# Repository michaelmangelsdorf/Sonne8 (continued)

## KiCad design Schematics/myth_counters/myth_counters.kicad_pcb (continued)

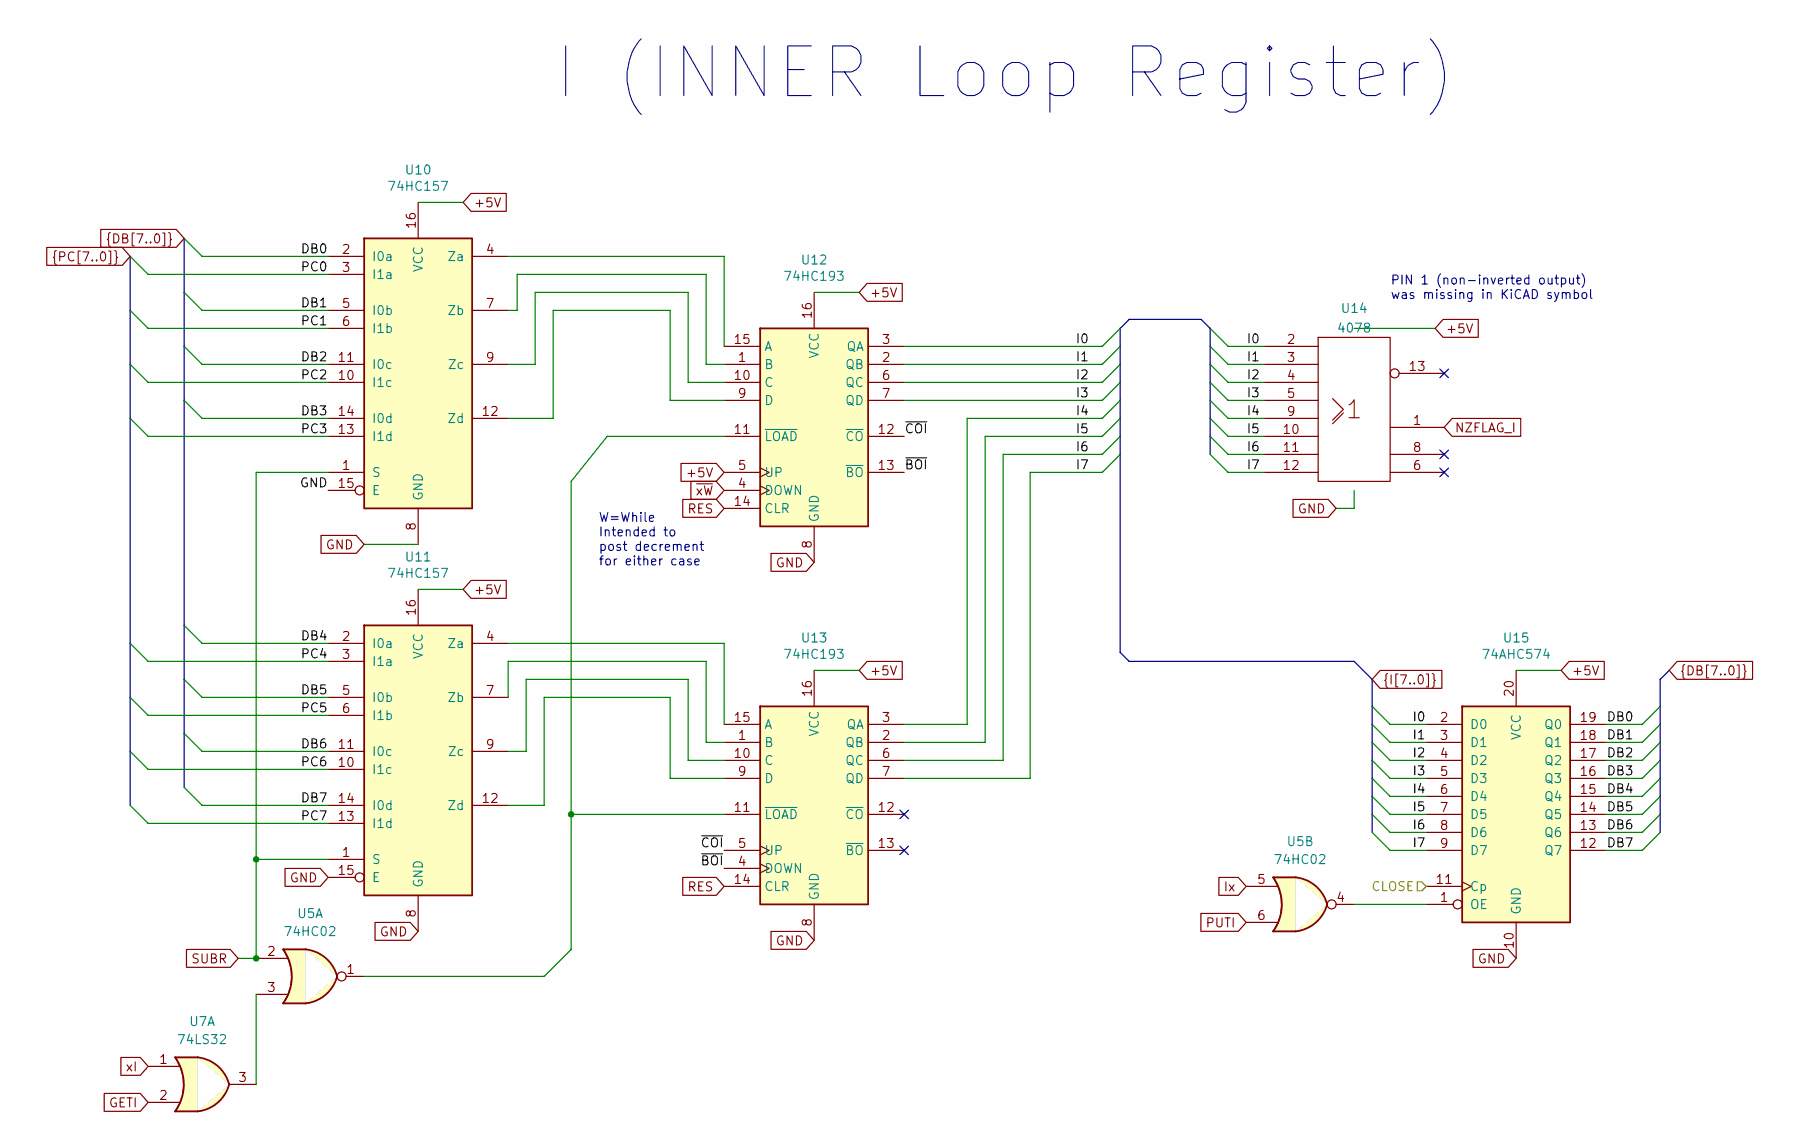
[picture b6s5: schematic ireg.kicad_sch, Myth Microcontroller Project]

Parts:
U5: 74HC02; DIP-14_W7.62mm_LongPads
U7: 74LS32; DIP-14_W7.62mm_LongPads
U10, U11: 74HC157; DIP-16_W7.62mm_Socket_LongPads
U12, U13: 74HC193; DIP-16_W7.62mm_Socket_LongPads
U14: 4078; DIP-14_W7.62mm_Socket_LongPads
U15: 74AHC574; DIP-20_W7.62mm_Socket_LongPads

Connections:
+5V: U10.16 (VCC), U11.16 (VCC), U12.5 (UP), U12.16 (VCC), U13.16 (VCC), U14.14 (Vdd), U15.20 (VCC); also elsewhere on the board
/I Register/CLOSE: U15.11 (Cp)
/I Register/~BOI: U12.13 (~BO), U13.4 (DOWN)
/I Register/~COI: U12.12 (~CO), U13.5 (UP)
DB0: U10.2 (I0a), U15.19 (Q0); also elsewhere on the board
DB1: U10.5 (I0b), U15.18 (Q1); also elsewhere on the board
DB2: U10.11 (I0c), U15.17 (Q2); also elsewhere on the board
DB3: U10.14 (I0d), U15.16 (Q3); also elsewhere on the board
DB4: U11.2 (I0a), U15.15 (Q4); also elsewhere on the board
DB5: U11.5 (I0b), U15.14 (Q5); also elsewhere on the board
DB6: U11.11 (I0c), U15.13 (Q6); also elsewhere on the board
DB7: U11.14 (I0d), U15.12 (Q7); also elsewhere on the board
GETI: U7.2
GND: U10.8 (GND), U10.15 (E), U11.8 (GND), U11.15 (E), U12.8 (GND), U13.8 (GND), U14.7 (Vss), U15.10 (GND); also elsewhere on the board
I0: U12.3 (QA), U14.2, U15.2 (D0); also elsewhere on the board
I1: U12.2 (QB), U14.3, U15.3 (D1); also elsewhere on the board
I2: U12.6 (QC), U14.4, U15.4 (D2); also elsewhere on the board
I3: U12.7 (QD), U14.5, U15.5 (D3); also elsewhere on the board
I4: U13.3 (QA), U14.9, U15.6 (D4); also elsewhere on the board
I5: U13.2 (QB), U14.10, U15.7 (D5); also elsewhere on the board
I6: U13.6 (QC), U14.11, U15.8 (D6); also elsewhere on the board
I7: U13.7 (QD), U14.12, U15.9 (D7); also elsewhere on the board
Ix: U5.5
NZFLAG_I: U14.1; also elsewhere on the board
unnamed: U5.3, U7.3
unnamed: U10.4 (Za), U12.15 (A)
unnamed: U10.7 (Zb), U12.1 (B)
unnamed: U10.9 (Zc), U12.10 (C)
unnamed: U10.12 (Zd), U12.9 (D)
unnamed: U11.4 (Za), U13.15 (A)
unnamed: U11.7 (Zb), U13.1 (B)
unnamed: U11.9 (Zc), U13.10 (C)
unnamed: U11.12 (Zd), U13.9 (D)
unnamed: U5.1, U12.11 (~LOAD), U13.11 (~LOAD)
unnamed: U5.4, U15.1 (OE)
PC0: U10.3 (I1a); also elsewhere on the board
PC1: U10.6 (I1b); also elsewhere on the board
PC2: U10.10 (I1c); also elsewhere on the board
PC3: U10.13 (I1d); also elsewhere on the board
PC4: U11.3 (I1a); also elsewhere on the board
PC5: U11.6 (I1b); also elsewhere on the board
PC6: U11.10 (I1c); also elsewhere on the board
PC7: U11.13 (I1d); also elsewhere on the board
PUTI: U5.6
RES: U12.14 (CLR), U13.14 (CLR); also elsewhere on the board
SUBR: U5.2, U10.1 (S), U11.1 (S)
xI: U7.1
~xW: U12.4 (DOWN)

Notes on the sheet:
PIN 1 (non-inverted output) was missing in KiCAD symbol
W=While Intended to post decrement for either case
I (INNER Loop Register)

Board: 2 copper layers, 48 parts (0 on the bottom side), 90 nets, no tracks yet.

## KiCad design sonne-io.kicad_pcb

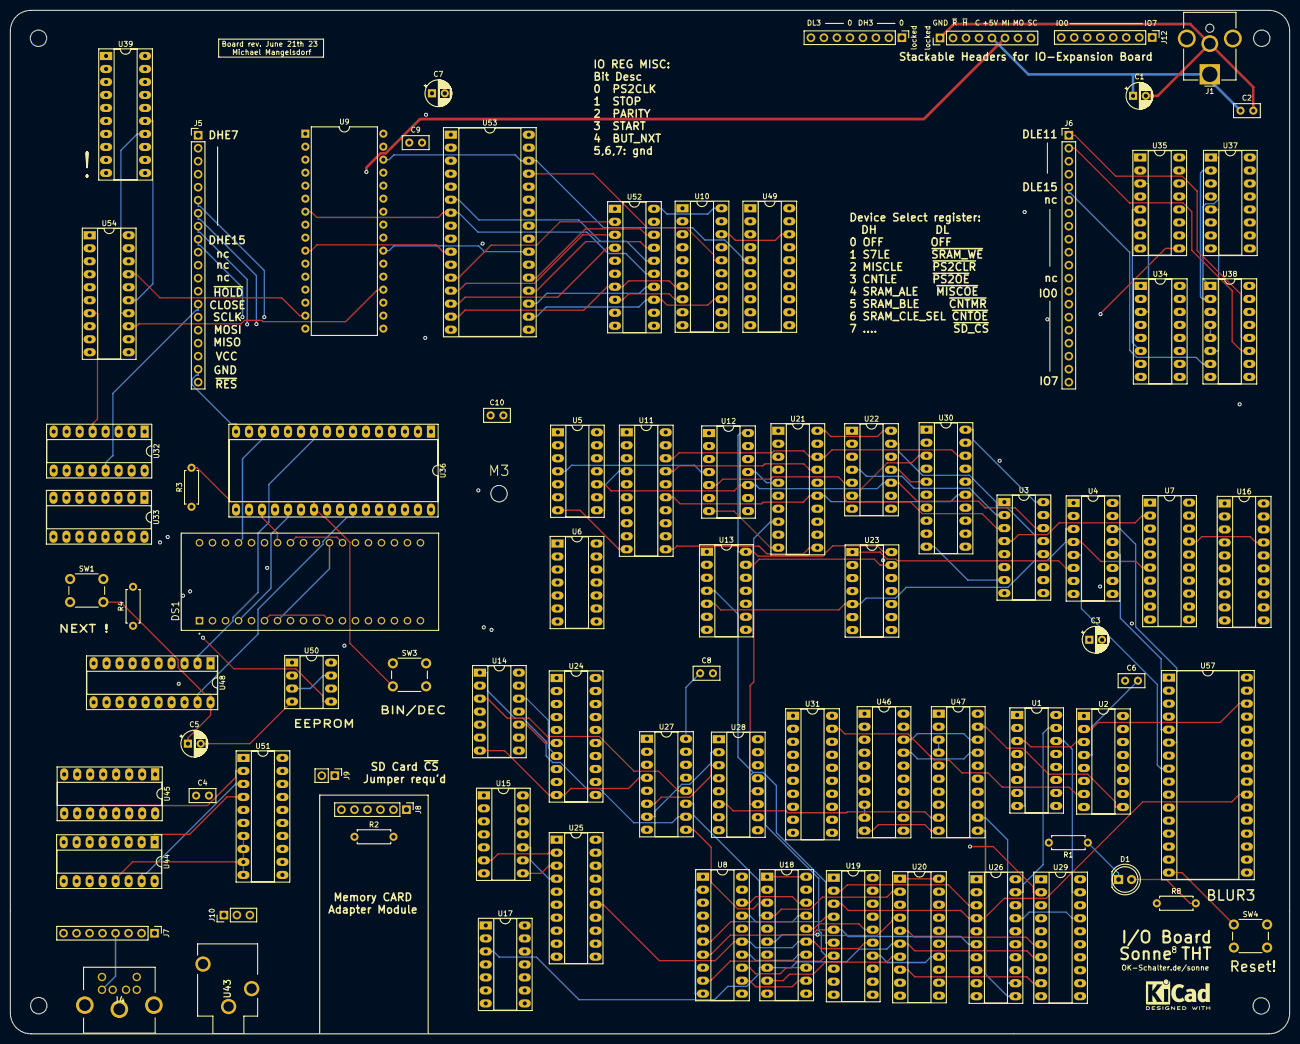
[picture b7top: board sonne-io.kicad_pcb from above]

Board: 4 copper layers, 250.0 x 200.0 mm, 83 parts (0 on the bottom side), 226 nets.

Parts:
C1, C3, C5, C7: C_Polarized_Small; CP_Radial_D5.0mm_P2.50mm
C2, C4, C6, C8, C9, C10: C_Small; C_Disc_D5.0mm_W2.5mm_P2.50mm
D1: LED; LED_D5.0mm
DS1: CA56-11EWA; LED_CA56-11EWA
J1: Barrel_Jack; BarrelJack_CUI_PJ-063AH_Horizontal_CircularHoles
J4: KMDGX-6S-BS; KMDGX6SBS
J5, J6: Conn_01x20_Male; PinHeader_1x20_P2.54mm_Vertical
J7, J12: Conn_01x08_Male; PinHeader_1x08_P2.54mm_Vertical
J8: Conn_01x06_Female; PinHeader_1x06_P2.54mm_Vertical
J9: Conn_01x02_Male; PinHeader_1x02_P2.54mm_Vertical
J10: Conn_01x03_Male; PinHeader_1x03_P2.54mm_Vertical
R1: 220; R_Axial_DIN0207_L6.3mm_D2.5mm_P7.62mm_Horizontal
R2: 100 Ohm; R_Axial_DIN0207_L6.3mm_D2.5mm_P7.62mm_Horizontal
R3: R_Small; R_Axial_DIN0207_L6.3mm_D2.5mm_P7.62mm_Horizontal
R4, R8: 1k; R_Axial_DIN0207_L6.3mm_D2.5mm_P7.62mm_Horizontal
SW1, SW4: SW_RES; SW_PUSH_6mm_H4.3mm
SW3: SW_BINDEC; SW_PUSH_6mm_H4.3mm
U1, U2, U37, U38: 74LS138; DIP-16_W7.62mm_Socket_LongPads
U3, U4: 74LS283; DIP-16_W7.62mm_Socket_LongPads
U5, U6: 74LS08; DIP-14_W7.62mm_Socket_LongPads
U7, U8, U11, U16, U18, U19, U20, U21, U24, U25, U26, U29, U30, U31, U46, U47: 74HC245; DIP-20_W7.62mm_Socket_LongPads
U9: AS6C4008-55PCN; DIP-32_W15.24mm
U10, U48, U49, U52: 74HC273; DIP-20_W7.62mm_Socket_LongPads
U12, U13: 74LS86; DIP-14_W7.62mm_Socket_LongPads
U14, U15, U17: 74AHC04; DIP-14_W7.62mm_Socket_LongPads
U22, U23: 74LS32; DIP-14_W7.62mm_Socket_LongPads
U27, U28: 74LS85; DIP-16_W7.62mm_Socket_LongPads
U32: 74HC590; DIP-16_W7.62mm_Socket_LongPads
U33, U34, U35: 74HC238; DIP-16_W7.62mm_Socket_LongPads
U36, U53: SST39SF040; DIP-32_W15.24mm_Socket_LongPads
U39: 74LS573; DIP-20_W7.62mm_Socket_LongPads
U43: SJ1-3513N; SJ13513N
U44, U45: 74HC595; DIP-16_W7.62mm_Socket_LongPads
U50: 25LCxxx; DIP-8_W7.62mm_Socket_LongPads
U51, U54: 74LS574; DIP-20_W7.62mm_Socket_LongPads
U57: 27C080; DIP-32_W15.24mm_Socket_LongPads
locked: Conn_01x08_Male; PinHeader_1x08_P2.54mm_Vertical
locked#2: Conn_01x08_Male; PinHeader_1x08_P2.54mm_Vertical

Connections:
/AD0: U9.12 (A0), U52.2 (Q0), U53.12 (A0)
/AD1: U9.11 (A1), U52.5 (Q1), U53.11 (A1)
/AD2: U9.10 (A2), U52.6 (Q2), U53.10 (A2)
/AD3: U9.9 (A3), U52.9 (Q3), U53.9 (A3)
/AD4: U9.8 (A4), U52.12 (Q4), U53.8 (A4)
/AD5: U9.7 (A5), U52.15 (Q5), U53.7 (A5)
/AD6: U9.6 (A6), U52.16 (Q6), U53.6 (A6)
/AD7: U9.5 (A7), U52.19 (Q7), U53.5 (A7)
/AD8: U9.27 (A8), U10.2 (Q0), U53.27 (A8)
/AD9: U9.26 (A9), U10.5 (Q1), U53.26 (A9)
/AD10: U9.23 (A10), U10.6 (Q2), U53.23 (A10)
/AD11: U9.25 (A11), U10.9 (Q3), U53.25 (A11)
/AD12: U9.4 (A12), U10.12 (Q4), U53.4 (A12)
/AD13: U9.28 (A13), U10.15 (Q5), U53.28 (A13)
/AD14: U9.3 (A14), U10.16 (Q6), U53.29 (A14)
/AD15: U9.31 (A15), U10.19 (Q7), U53.3 (A15)
/AD16: U9.2 (A16), U49.2 (Q0), U53.2 (A16)
/AD17: U9.30 (A17), U49.5 (Q1), U53.30 (A17)
/AD18: U9.1 (A18), U49.6 (Q2), U53.1 (A18)
/ADD: U2.12 (O3), U7.19 (CE)
/AEB: U2.9 (O6), U47.19 (CE)
/AGB: U2.7 (O7), U31.19 (CE)
/ALB: U2.10 (O5), U46.19 (CE)
/AND: U2.15 (O0), U11.19 (CE)
/AND0: U5.3, U11.2 (A0)
/AND1: U5.6, U11.3 (A1)
/AND2: U5.8, U11.4 (A2)
/AND3: U5.11, U11.5 (A3)
/AND4: U6.3, U11.6 (A4)
/AND5: U6.6, U11.7 (A5)
/AND6: U6.8, U11.8 (A6)
/AND7: U6.11, U11.9 (A7)
/BIN_OPC0: U1.1 (A0), U2.1 (A0), U57.2 (A16)
/BIN_OPC1: U1.2 (A1), U2.2 (A1), U57.30 (A17)
/BIN_OPC2: U1.3 (A2), U2.3 (A2), U57.31 (A18)
/BIN_OPC3: U1.4 (E1), U2.6 (E3), U57.1 (A19)
/BUT_NXT: R4.2, SW1.1, U51.6 (D4)
/CLOSE: J5.14, U32.11 (CPC), U32.13 (CPR), locked.4
/CNTLE: U35.12 (Y3), U54.11 (Cp)
/CYB: U2.11 (O4), U16.19 (CE)
/DH0: U34.1 (A0), U35.1 (A0), locked#2.1
/DH1: U34.2 (A1), U35.2 (A1), locked#2.2
/DH2: U34.3 (A2), U35.3 (A2), locked#2.3
/DH3: U34.6 (G1), U35.4 (~G2A), U35.5 (~G2B), locked#2.4
/DHE7: J5.1, U35.7 (Y7)
/DHE8: J5.2, U34.15 (Y0)
/DHE9: J5.3, U34.14 (Y1)
/DHE10: J5.4, U34.13 (Y2)
/DHE11: J5.5, U34.12 (Y3)
/DHE12: J5.6, U34.11 (Y4)
/DHE13: J5.7, U34.10 (Y5)
/DHE14: J5.8, U34.9 (Y6)
/DHE15: J5.9, U34.7 (Y7)
/DL0: U37.1 (A0), U38.1 (A0), locked#2.5
/DL1: U37.2 (A1), U38.2 (A1), locked#2.6
/DL2: U37.3 (A2), U38.3 (A2), locked#2.7
/DL3: U37.4 (E1), U37.5 (E2), U38.6 (E3), locked#2.8
/DLE11: J6.1, U38.12 (O3)
/DLE12: J6.2, U38.11 (O4)
/DLE13: J6.3, U38.10 (O5)
/DLE14: J6.4, U38.9 (O6)
/DLE15: J6.5, U38.7 (O7)
/E0: DS1.32, U33.15 (Y0)
/E1: DS1.31, U33.14 (Y1)
/E2: DS1.23, U33.13 (Y2)
/E3: DS1.22, U33.12 (Y3)
/EOR: U2.13 (O2), U21.19 (CE)
/EOR0: U12.3, U21.2 (A0)
/EOR1: U12.6, U21.3 (A1)
/EOR2: U12.8, U21.4 (A2)
/EOR3: U12.11, U21.5 (A3)
/EOR4: U13.3, U21.6 (A4)
/EOR5: U13.6, U21.7 (A5)
/EOR6: U13.8, U21.8 (A6)
/EOR7: U13.11, U21.9 (A7)
/IDA: U1.15 (O0), U26.19 (CE)
/IDB: U1.14 (O1), U29.19 (CE)
/IO0: J6.13, J12.8, U9.13 (DQ0), U10.3 (D0), U39.19 (Q0), U48.3 (D0), U49.3 (D0), U51.19 (Q0), U52.3 (D0), U53.13 (D0), U54.19 (Q0)
/IO1: J6.14, J12.7, U9.14 (DQ1), U10.4 (D1), U39.18 (Q1), U48.4 (D1), U49.4 (D1), U51.18 (Q1), U52.4 (D1), U53.14 (D1), U54.18 (Q1)
/IO2: J6.15, J12.6, U9.15 (DQ2), U10.7 (D2), U39.17 (Q2), U48.7 (D2), U49.7 (D2), U51.17 (Q2), U52.7 (D2), U53.15 (D2), U54.17 (Q2)
/IO3: J6.16, J12.5, U9.17 (DQ3), U10.8 (D3), U39.16 (Q3), U48.8 (D3), U49.8 (D3), U51.16 (Q3), U52.8 (D3), U53.17 (D3), U54.16 (Q3)
/IO4: J6.17, J12.4, U9.18 (DQ4), U10.13 (D4), U39.15 (Q4), U48.13 (D4), U49.13 (D4), U51.15 (Q4), U52.13 (D4), U53.18 (D4), U54.15 (Q4)
/IO5: J6.18, J12.3, U9.19 (DQ5), U10.14 (D5), U39.14 (Q5), U48.14 (D5), U49.14 (D5), U51.14 (Q5), U52.14 (D5), U53.19 (D5), U54.14 (Q5)
/IO6: J6.19, J12.2, U9.20 (DQ6), U10.17 (D6), U39.13 (Q6), U48.17 (D6), U49.17 (D6), U51.13 (Q6), U52.17 (D6), U53.20 (D6), U54.13 (Q6)
/IO7: J6.20, J12.1, U9.21 (DQ7), U10.18 (D7), U39.12 (Q7), U48.18 (D7), U49.18 (D7), U51.12 (Q7), U52.18 (D7), U53.21 (D7), U54.12 (Q7)
/IOR: U2.14 (O1), U30.19 (CE)
/IOR0: U22.3, U30.2 (A0)
/IOR1: U22.6, U30.3 (A1)
/IOR2: U22.8, U30.4 (A2)
/IOR3: U22.11, U30.5 (A3)
/IOR4: U23.3, U30.6 (A4)
/IOR5: U23.6, U30.7 (A5)
/IOR6: U23.8, U30.8 (A6)
/IOR7: U23.11, U30.9 (A7)
/MISCLE: U35.13 (Y2), U51.11 (Cp)
/MISO: J5.17, J8.3, U50.2 (MISO), locked.6
/MOSI: J5.16, J8.4, U50.5 (MOSI), locked.7
/NOTRA0: U14.2, U24.2 (A0)
/NOTRA1: U14.4, U24.3 (A1)
/NOTRA2: U14.6, U24.4 (A2)
/NOTRA3: U14.8, U24.5 (A3)
/NOTRA4: U14.10, U24.6 (A4)
/NOTRA5: U14.12, U24.7 (A5)
/NOTRA6: U15.2, U24.8 (A6)
/NOTRA7: U15.4, U24.9 (A7)
/NOTRB0: U15.6, U25.2 (A0)
/NOTRB1: U15.8, U25.3 (A1)
/NOTRB2: U15.10, U25.4 (A2)
/NOTRB3: U15.12, U25.5 (A3)
/NOTRB4: U17.2, U25.6 (A4)
/NOTRB5: U17.4, U25.7 (A5)
/NOTRB6: U17.6, U25.8 (A6)
/NOTRB7: U17.8, U25.9 (A7)
/OCA: U1.13 (O2), U24.19 (CE)
/OCB: U1.12 (O3), U25.19 (CE)
/PARITY: U44.1 (QB), U51.4 (D2)
/PS2CLK: J4.6, J7.5, U44.11 (SRCLK), U44.12 (RCLK), U45.11 (SRCLK), U45.12 (RCLK), U51.2 (D0)
/PS2DATA: J4.1, J7.1, U44.14 (SER)
/PSB0: U39.2 (D0), U45.1 (QB)
/PSB1: U39.3 (D1), U45.15 (QA)
/PSB2: U39.4 (D2), U44.7 (QH)
/PSB3: U39.5 (D3), U44.6 (QG)
/PSB4: U39.6 (D4), U44.5 (QF)
/PSB5: U39.7 (D5), U44.4 (QE)
/PSB6: U39.8 (D6), U44.3 (QD)
/PSB7: U39.9 (D7), U44.2 (QC)
/Q0: U32.15 (Q0), U54.2 (D0)
/Q1: U32.1 (Q1), U54.3 (D1)
/Q2: U32.2 (Q2), U54.4 (D2)
/Q3: U32.3 (Q3), U54.5 (D3)
/Q4: U32.4 (Q4), U54.6 (D4)
/Q5: U32.5 (Q5), U54.7 (D5)
/Q6: U32.6 (Q6), U33.1 (A0), U36.12 (A0), U54.8 (D6)
/Q7: U32.7 (Q7), U33.2 (A1), U36.11 (A1), U54.9 (D7)
/R0: U7.18 (B0), U8.18 (B0), U11.18 (B0), U16.18 (B0), U18.18 (B0), U19.18 (B0), U20.18 (B0), U21.18 (B0), U24.18 (B0), U25.18 (B0), U26.18 (B0), U29.18 (B0), U30.18 (B0), U31.18 (B0), U46.18 (B0), U47.18 (B0), U57.13 (D0)
/R1: U7.17 (B1), U8.17 (B1), U11.17 (B1), U16.17 (B1), U18.17 (B1), U19.17 (B1), U20.17 (B1), U21.17 (B1), U24.17 (B1), U25.17 (B1), U26.17 (B1), U29.17 (B1), U30.17 (B1), U31.17 (B1), U46.17 (B1), U47.17 (B1), U57.14 (D1)
/R2: U7.16 (B2), U8.16 (B2), U11.16 (B2), U16.16 (B2), U18.16 (B2), U19.16 (B2), U20.16 (B2), U21.16 (B2), U24.16 (B2), U25.16 (B2), U26.16 (B2), U29.16 (B2), U30.16 (B2), U31.16 (B2), U46.16 (B2), U47.16 (B2), U57.15 (D2)
/R3: U7.15 (B3), U8.15 (B3), U11.15 (B3), U16.15 (B3), U18.15 (B3), U19.15 (B3), U20.15 (B3), U21.15 (B3), U24.15 (B3), U25.15 (B3), U26.15 (B3), U29.15 (B3), U30.15 (B3), U31.15 (B3), U46.15 (B3), U47.15 (B3), U57.17 (D3)
/R4: U7.14 (B4), U8.14 (B4), U11.14 (B4), U16.14 (B4), U18.14 (B4), U19.14 (B4), U20.14 (B4), U21.14 (B4), U24.14 (B4), U25.14 (B4), U26.14 (B4), U29.14 (B4), U30.14 (B4), U31.14 (B4), U46.14 (B4), U47.14 (B4), U57.18 (D4)
/R5: U7.13 (B5), U8.13 (B5), U11.13 (B5), U16.13 (B5), U18.13 (B5), U19.13 (B5), U20.13 (B5), U21.13 (B5), U24.13 (B5), U25.13 (B5), U26.13 (B5), U29.13 (B5), U30.13 (B5), U31.13 (B5), U46.13 (B5), U47.13 (B5), U57.19 (D5)
/R6: U7.12 (B6), U8.12 (B6), U11.12 (B6), U16.12 (B6), U18.12 (B6), U19.12 (B6), U20.12 (B6), U21.12 (B6), U24.12 (B6), U25.12 (B6), U26.12 (B6), U29.12 (B6), U30.12 (B6), U31.12 (B6), U46.12 (B6), U47.12 (B6), U57.20 (D6)
/R7: U7.11 (B7), U8.11 (B7), U11.11 (B7), U16.11 (B7), U18.11 (B7), U19.11 (B7), U20.11 (B7), U21.11 (B7), U24.11 (B7), U25.11 (B7), U26.11 (B7), U29.11 (B7), U30.11 (B7), U31.11 (B7), U46.11 (B7), U47.11 (B7), U57.21 (D7)
/RA0: U3.6 (B1), U5.1, U8.3 (A1), U12.1, U14.1, U22.1, U26.2 (A0), U27.10 (A0), U57.27 (A8)
/RA1: U3.2 (B2), U5.4, U8.4 (A2), U12.4, U14.3, U19.2 (A0), U22.4, U26.3 (A1), U27.12 (A1), U57.26 (A9)
/RA2: U3.15 (B3), U5.9, U8.5 (A3), U12.9, U14.5, U19.3 (A1), U22.9, U26.4 (A2), U27.13 (A2), U57.23 (A10)
/RA3: U3.11 (B4), U5.12, U8.6 (A4), U12.12, U14.9, U19.4 (A2), U22.12, U26.5 (A3), U27.15 (A3), U57.25 (A11)
/RA4: U4.6 (B1), U6.1, U8.7 (A5), U13.1, U14.11, U19.5 (A3), U23.1, U26.6 (A4), U28.10 (A0), U57.4 (A12)
/RA5: U4.2 (B2), U6.4, U8.8 (A6), U13.4, U14.13, U19.6 (A4), U23.4, U26.7 (A5), U28.12 (A1), U57.28 (A13)
/RA6: U4.15 (B3), U6.9, U8.9 (A7), U13.9, U15.1, U19.7 (A5), U23.9, U26.8 (A6), U28.13 (A2), U57.29 (A14)
/RA7: U4.11 (B4), U6.12, U13.12, U15.3, U19.8 (A6), U23.12, U26.9 (A7), U28.15 (A3), U57.3 (A15)
/RB0: U3.5 (A1), U5.2, U12.2, U15.5, U18.3 (A1), U22.2, U27.9 (B0), U29.2 (A0), U57.12 (A0)
/RB1: U3.3 (A2), U5.5, U12.5, U15.9, U18.4 (A2), U20.2 (A0), U22.5, U27.11 (B1), U29.3 (A1), U57.11 (A1)
/RB2: U3.14 (A3), U5.10, U12.10, U15.11, U18.5 (A3), U20.3 (A1), U22.10, U27.14 (B2), U29.4 (A2), U57.10 (A2)
/RB3: U3.12 (A4), U5.13, U12.13, U15.13, U18.6 (A4), U20.4 (A2), U22.13, U27.1 (B3), U29.5 (A3), U57.9 (A3)
/RB4: U4.5 (A1), U6.2, U13.2, U17.1, U18.7 (A5), U20.5 (A3), U23.2, U28.9 (B0), U29.6 (A4), U57.8 (A4)
/RB5: U4.3 (A2), U6.5, U13.5, U17.3, U18.8 (A6), U20.6 (A4), U23.5, U28.11 (B1), U29.7 (A5), U57.7 (A5)
/RB6: U4.14 (A3), U6.10, U13.10, U17.5, U18.9 (A7), U20.7 (A5), U23.10, U28.14 (B2), U29.8 (A6), U57.6 (A6)
/RB7: U4.12 (A4), U6.13, U13.13, U17.9, U20.8 (A6), U23.13, U28.1 (B3), U29.9 (A7), U57.5 (A7)
/RING: J10.1, U43.3 (RING)
/S7D0: U36.10 (A2), U48.2 (Q0)
/S7D1: U36.9 (A3), U48.5 (Q1)
/S7D2: U36.8 (A4), U48.6 (Q2)
/S7D3: U36.7 (A5), U48.9 (Q3)
/S7D4: U36.6 (A6), U48.12 (Q4)
/S7D5: U36.5 (A7), U48.15 (Q5)
/S7D6: U36.27 (A8), U48.16 (Q6)
/S7D7: U36.26 (A9), U48.19 (Q7)
/S7LE: U35.14 (Y1), U48.11 (Cp)
/SCLK: J5.15, J8.5, R2.1, U50.6 (SCK), locked.8
/SLA: U1.11 (O4), U8.19 (CE)
/SLB: U1.10 (O5), U18.19 (CE)
/SLEEVE: J10.2, U43.1 (SLEEVE)
/SRA: U1.9 (O6), U19.19 (CE)
/SRAM_ALE: U35.11 (Y4), U52.11 (Cp)
/SRAM_BLE: U10.11 (Cp), U35.10 (Y5)
/SRAM_CLE_SEL: U35.9 (Y6), U49.11 (Cp)
/SRB: U1.7 (O7), U20.19 (CE)
/START: U45.2 (QC), U51.5 (D3)
/STOP: U44.15 (QA), U51.3 (D1)
/Sa: DS1.20, DS1.25, DS1.29, DS1.34, U36.13 (D0)
/Sb: DS1.19, DS1.24, DS1.28, DS1.33, U36.14 (D1)
/Sc: DS1.3, DS1.8, DS1.12, DS1.17, U36.15 (D2)
/Sd: DS1.2, DS1.6, DS1.11, DS1.15, U36.17 (D3)
/Sdp: DS1.4, DS1.9, DS1.13, DS1.18, U36.21 (D7)
/Se: DS1.1, DS1.5, DS1.10, DS1.14, U36.18 (D4)
/Sf: DS1.21, DS1.27, DS1.30, DS1.36, U36.19 (D5)
/Sg: DS1.7, DS1.16, DS1.26, DS1.35, U36.20 (D6)
/TIP: J10.3, U43.2 (TIP)
/~CNTMR: U32.10 (~MRC), U37.10 (O5)
/~CNTOE: U37.9 (O6), U54.1 (OE)
/~EEP_CS: U38.15 (O0), U50.1 (~CS)
/~HOLD: J5.13, locked.3
/~MISCOE: U37.11 (O4), U51.1 (OE)
/~PS2CLR: U37.13 (O2), U44.10 (~SRCLR), U45.10 (~SRCLR)
/~PS2OE: U37.12 (O3), U39.1 (OE)
/~RES: J5.20, R8.1, SW4.2, U48.1 (~Mr), locked.2
/~SD_CS: J9.2, U37.7 (O7)
/~SRAMA_CLR: U10.1 (~Mr), U38.14 (O1), U49.1 (~Mr), U52.1 (~Mr)
/~SRAM_OE: U9.24 (OE#), U38.13 (O2), U53.24 (OE)
/~SRAM_WE: U9.29 (WE#), U37.14 (O1)
GND: C1.2, C2.2, C3.2, C4.2, C5.2, C6.2, C7.2, C8.2, C9.2, C10.2, J1.2, J4.3, J4.MH1, J4.MH2, J4.MH3, J5.19, J7.3, J7.7, J7.8, J8.1, R1.2, R2.2, R4.1, SW3.1, SW4.1, U1.5 (E2), U1.8 (GND), U2.4 (E1), U2.5 (E2), U2.8 (GND), U3.7 (C0), U3.8 (GND), U4.8 (GND), U5.7 (GND), U6.7 (GND), U7.10 (GND), U8.2 (A0), U8.10 (GND), U9.16 (VSS), U10.10 (GND), U11.10 (GND), U12.7 (GND), U13.7 (GND), U14.7 (GND), U15.7 (GND), U16.3 (A1), U16.4 (A2), U16.5 (A3), U16.6 (A4), U16.7 (A5), U16.8 (A6), U16.9 (A7), U16.10 (GND), U17.7 (GND), U17.13, U18.2 (A0), U18.10 (GND), U19.9 (A7), U19.10 (GND), U20.9 (A7), U20.10 (GND), U21.10 (GND), U22.7 (GND), U23.7 (GND), U24.10 (GND), U25.10 (GND), U26.10 (GND), U27.2 (Ia<b), U27.3 (Ia=b), U27.4 (Ia>b), U27.8 (GND), U28.8 (GND), U29.10 (GND), U30.10 (GND), U31.10 (GND), U32.8 (GND), U32.12 (~CE), U32.14 (~OE), U33.3 (A2), U33.4 (~G2A), U33.5 (~G2B), U33.8 (GND), U34.4 (~G2A), U34.5 (~G2B), U34.8 (GND), U35.8 (GND), U36.1 (A18), U36.2 (A16), U36.3 (A15), U36.4 (A12), U36.16 (GND), U36.22 (CE), U36.24 (OE), U36.25 (A11), U36.28 (A13), U36.29 (A14), U36.30 (A17), U37.8 (GND), U38.4 (E1), U38.5 (E2), U38.8 (GND), U39.10 (GND), U44.8 (GND), U44.13 (~OE), U45.8 (GND), U45.13 (~OE), U46.10 (GND), U47.10 (GND), U48.10 (GND), U49.10 (GND), U50.4 (GND), U51.7 (D5), U51.8 (D6), U51.9 (D7), U51.10 (GND), U52.10 (GND), U53.16 (GND), U54.10 (GND), U57.16 (GND), U57.22 (~CE), U57.24 (~OE), locked.1
unnamed: D1.1 (K), R1.1
unnamed: J4.2, J7.2
unnamed: J4.8, J7.6
unnamed: J8.6, J9.1
unnamed: U3.9 (C4), U4.7 (C0)
unnamed: U3.4 (S1), U7.2 (A0)
unnamed: U3.1 (S2), U7.3 (A1)
unnamed: U3.13 (S3), U7.4 (A2)
unnamed: U3.10 (S4), U7.5 (A3)
unnamed: U4.4 (S1), U7.6 (A4)
unnamed: U4.1 (S2), U7.7 (A5)
unnamed: U4.13 (S3), U7.8 (A6)
unnamed: U4.10 (S4), U7.9 (A7)
unnamed: U4.9 (C4), U16.2 (A0)
unnamed: U27.7 (Oa<b), U28.2 (Ia<b)
unnamed: U27.6 (Oa=b), U28.3 (Ia=b)
unnamed: U27.5 (Oa>b), U28.4 (Ia>b)
unnamed: U28.7 (Oa<b), U46.2 (A0), U46.3 (A1), U46.4 (A2), U46.5 (A3), U46.6 (A4), U46.7 (A5), U46.8 (A6), U46.9 (A7)
unnamed: U28.6 (Oa=b), U47.2 (A0), U47.3 (A1), U47.4 (A2), U47.5 (A3), U47.6 (A4), U47.7 (A5), U47.8 (A6), U47.9 (A7)
unnamed: U28.5 (Oa>b), U31.2 (A0), U31.3 (A1), U31.4 (A2), U31.5 (A3), U31.6 (A4), U31.7 (A5), U31.8 (A6), U31.9 (A7)
unnamed: R3.2, SW3.2, U36.23 (A10)
unnamed: U44.9 (QH'), U45.14 (SER)
unnamed: U9.22 (CE#), U17.11, U49.9 (Q3)
unnamed: U17.10, U53.22 (CE)
VCC: C1.1, C2.1, C3.1, C4.1, C5.1, C6.1, C7.1, C8.1, C9.1, C10.1, D1.2 (A), J1.1, J4.5, J5.18, J7.4, J8.2, R3.1, R8.2, SW1.2, U1.6 (E3), U1.16 (VCC), U2.16 (VCC), U3.16 (VCC), U4.16 (VCC), U5.14 (VCC), U6.14 (VCC), U7.1 (A->B), U7.20 (VCC), U8.1 (A->B), U8.20 (VCC), U9.32 (VCC), U10.20 (VCC), U11.1 (A->B), U11.20 (VCC), U12.14 (VCC), U13.14 (VCC), U14.14 (VCC), U15.14 (VCC), U16.1 (A->B), U16.20 (VCC), U17.14 (VCC), U18.1 (A->B), U18.20 (VCC), U19.1 (A->B), U19.20 (VCC), U20.1 (A->B), U20.20 (VCC), U21.1 (A->B), U21.20 (VCC), U22.14 (VCC), U23.14 (VCC), U24.1 (A->B), U24.20 (VCC), U25.1 (A->B), U25.20 (VCC), U26.1 (A->B), U26.20 (VCC), U27.16 (VCC), U28.16 (VCC), U29.1 (A->B), U29.20 (VCC), U30.1 (A->B), U30.20 (VCC), U31.1 (A->B), U31.20 (VCC), U32.16 (VCC), U33.6 (G1), U33.16 (VCC), U34.16 (VCC), U35.6 (G1), U35.16 (VCC), U36.31 (PGM), U36.32 (VCC), U37.6 (E3), U37.16 (VCC), U38.16 (VCC), U39.11 (Cp), U39.20 (VCC), U44.16 (VCC), U45.16 (VCC), U46.1 (A->B), U46.20 (VCC), U47.1 (A->B), U47.20 (VCC), U48.20 (VCC), U49.20 (VCC), U50.3 (~WP), U50.7 (~HOLD), U50.8 (VCC), U51.20 (VCC), U52.20 (VCC), U53.31 (PGM), U53.32 (VCC), U54.20 (VCC), U57.32 (VCC), locked.5
